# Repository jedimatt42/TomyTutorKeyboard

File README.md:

# TomyTutorKeyboard
A PCBoard design for replacing Tomy Tutor Computer keyboard.

## Status
This is tested. Works great.

## Files

Schematic is here based on KiCAD.

* gerbers - folder with the rendered gerbers
* tomy_tutor_keyboard.scad - OpenSCAD model design file for framing
* tomy_tutor_keyboard.stl - STL file output ready for your favority slicer

# BOM

## 1. Printed Circuit Board

You'll need the bare pcb, see the design files here in this repo.

## 2. 57 MX1A-11NW key switches or equivalent:

The pcboard footprint is specific to these switches. But there are some variety that have the same footprint.

[mouser switches](https://www.mouser.com/ProductDetail/540-MX1A-11NW)

## 3. set of key stabalizers for the wide keys:

[ebay stabalizers](https://www.ebay.com/itm/322528567052?ViewItem=&item=322528567052&ppid=PPX000608&cnac=US&rsta=en_US(en_US)&cust=1SW22173KD939402H&unptid=b421f75c-4e70-11e8-8929-441ea1472df0&t=&cal=b3a4b6dd50c6e&calc=b3a4b6dd50c6e&calf=b3a4b6dd50c6e&unp_tpcid=email-receipt-auction-payment&page=main:email&pgrp=main:email&e=op&mchn=em&s=ci&mail=sys)

## 4. Cable

16 female to female dupont style jumper wires

## 5. 16 pin single inline 2.54mm right angle header

The header on the keyboard pcb is mounted on the underside of the board with the right angle pins facing forward.

## 6. 16 pin single inline 2.54mm straight header

I desoldered and removed the existing film cable connector from the Tomy Tutor motherboard, and replaced it with a row of 16 2.54mm spaced headers.

## 7. Key caps

I used a set of PC keyboard keycaps with a diminutive print. If you can find some with no print, that would be closer to ideal. You'll never find ones that match the Tomy keyboard map.  I found mine on ebay.

## 8. Transparent adhesive printer sheet. 

I printed my key labels on a sheet of adhesive transparency with a laser printer. Then cut out each label and applied it to the keycaps after they were in place. Not the most ideal.

[amazon - Avery self adhesive laminating sheets](https://smile.amazon.com/gp/product/B00006IC7H/ref=ppx_yo_dt_b_search_asin_title?ie=UTF8&psc=1)

NOTE: with regret, I cannot find the document I created with the custom keycap labels...

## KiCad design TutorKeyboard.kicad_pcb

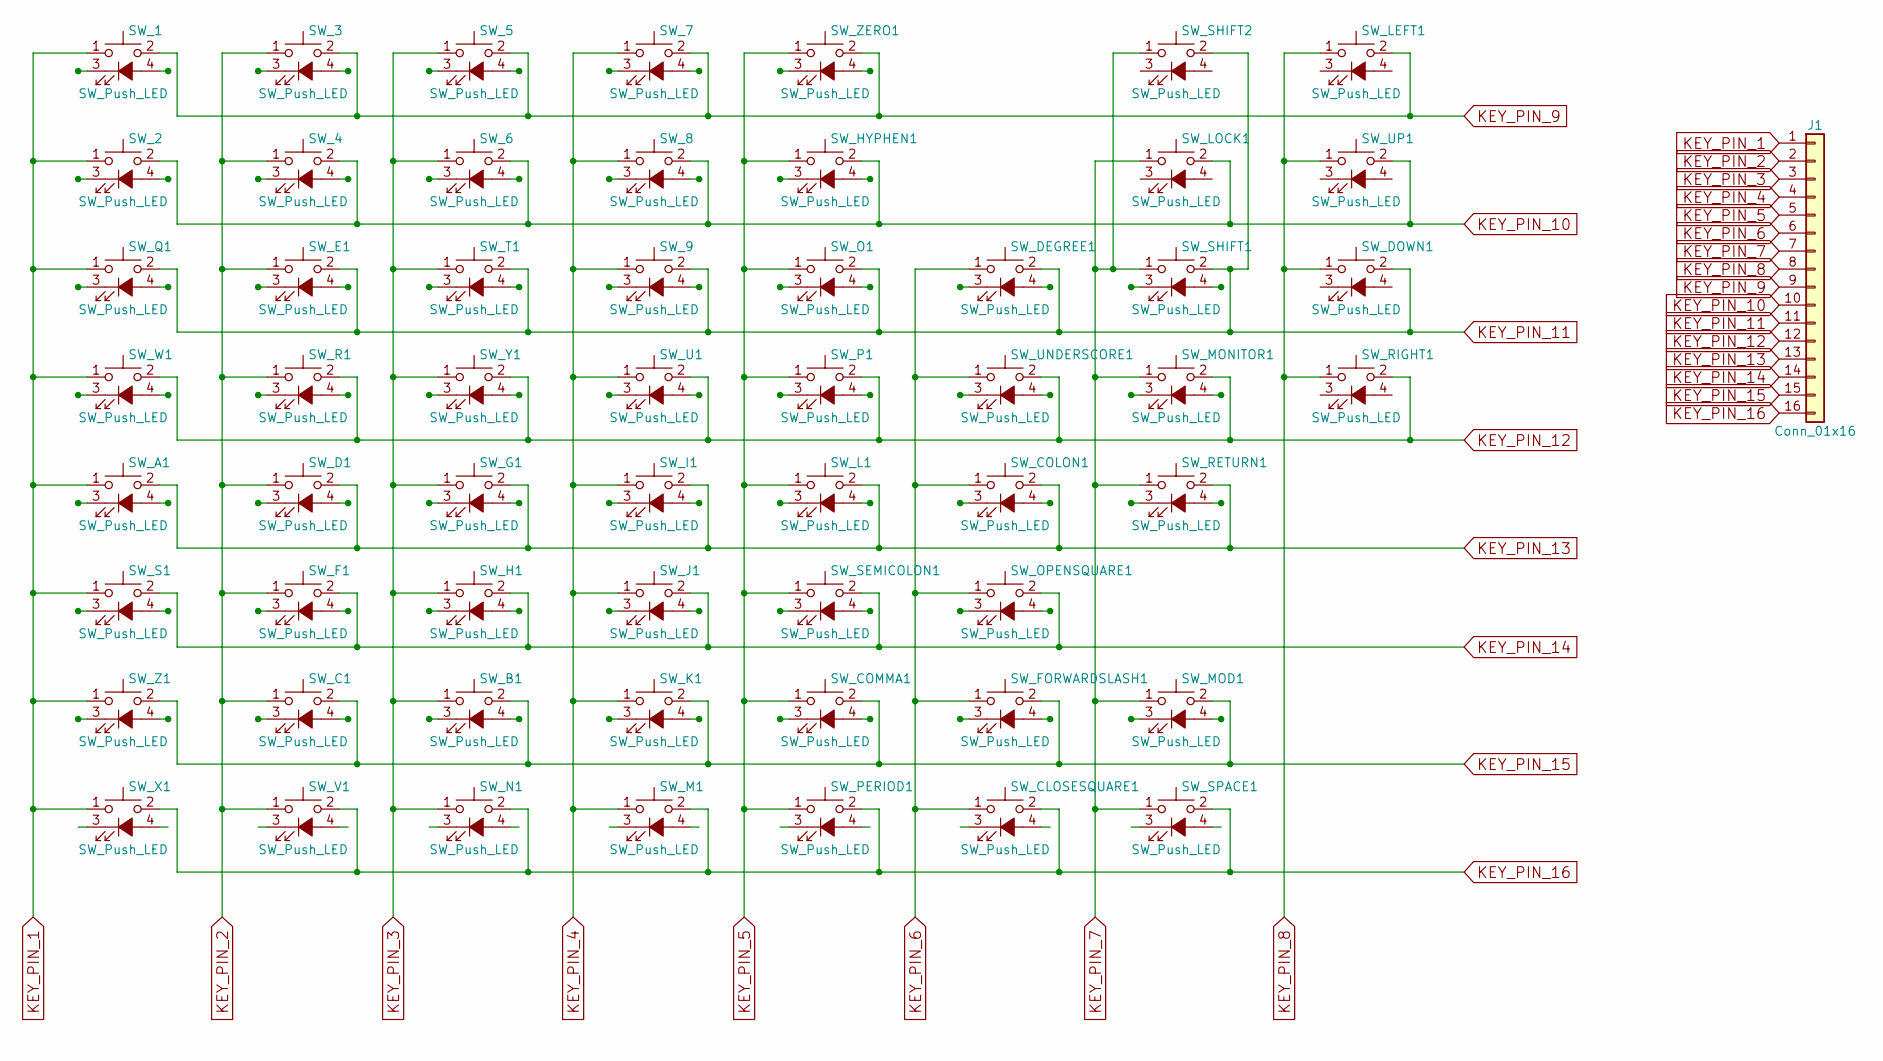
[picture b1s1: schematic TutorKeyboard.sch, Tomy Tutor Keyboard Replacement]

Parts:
J1: Conn_01x16; Pin_Header_Angled_1x16_Pitch2.54mm
SW_1, SW_2, SW_3, SW_4, SW_5, SW_6, SW_7, SW_8, SW_9: SW_Push_LED; SW_Cherry_MX1A_1.00u_PCB
SW_A1: SW_Push_LED; SW_Cherry_MX1A_1.00u_PCB
SW_B1: SW_Push_LED; SW_Cherry_MX1A_1.00u_PCB
SW_C1: SW_Push_LED; SW_Cherry_MX1A_1.00u_PCB
SW_CLOSESQUARE1: SW_Push_LED; SW_Cherry_MX1A_1.00u_PCB
SW_COLON1: SW_Push_LED; SW_Cherry_MX1A_1.00u_PCB
SW_COMMA1: SW_Push_LED; SW_Cherry_MX1A_1.00u_PCB
SW_D1: SW_Push_LED; SW_Cherry_MX1A_1.00u_PCB
SW_DEGREE1: SW_Push_LED; SW_Cherry_MX1A_1.00u_PCB
SW_DOWN1: SW_Push_LED; SW_Cherry_MX1A_1.00u_PCB
SW_E1: SW_Push_LED; SW_Cherry_MX1A_1.00u_PCB
SW_F1: SW_Push_LED; SW_Cherry_MX1A_1.00u_PCB
SW_FORWARDSLASH1: SW_Push_LED; SW_Cherry_MX1A_1.00u_PCB
SW_G1: SW_Push_LED; SW_Cherry_MX1A_1.00u_PCB
SW_H1: SW_Push_LED; SW_Cherry_MX1A_1.00u_PCB
SW_HYPHEN1: SW_Push_LED; SW_Cherry_MX1A_1.00u_PCB
SW_I1: SW_Push_LED; SW_Cherry_MX1A_1.00u_PCB
SW_J1: SW_Push_LED; SW_Cherry_MX1A_1.00u_PCB
SW_K1: SW_Push_LED; SW_Cherry_MX1A_1.00u_PCB
SW_L1: SW_Push_LED; SW_Cherry_MX1A_1.00u_PCB
SW_LEFT1: SW_Push_LED; SW_Cherry_MX1A_1.00u_PCB
SW_LOCK1: SW_Push_LED; SW_Cherry_MX1A_1.75u_PCB
SW_M1: SW_Push_LED; SW_Cherry_MX1A_1.00u_PCB
SW_MOD1: SW_Push_LED; SW_Cherry_MX1A_1.00u_PCB
SW_MONITOR1: SW_Push_LED; SW_Cherry_MX1A_1.00u_PCB
SW_N1: SW_Push_LED; SW_Cherry_MX1A_1.00u_PCB
SW_O1: SW_Push_LED; SW_Cherry_MX1A_1.00u_PCB
SW_OPENSQUARE1: SW_Push_LED; SW_Cherry_MX1A_1.00u_PCB
SW_P1: SW_Push_LED; SW_Cherry_MX1A_1.00u_PCB
SW_PERIOD1: SW_Push_LED; SW_Cherry_MX1A_1.00u_PCB
SW_Q1: SW_Push_LED; SW_Cherry_MX1A_1.00u_PCB
SW_R1: SW_Push_LED; SW_Cherry_MX1A_1.00u_PCB
SW_RETURN1: SW_Push_LED; SW_Cherry_MX1A_2.25u_PCB
SW_RIGHT1: SW_Push_LED; SW_Cherry_MX1A_1.00u_PCB
SW_S1: SW_Push_LED; SW_Cherry_MX1A_1.00u_PCB
SW_SEMICOLON1: SW_Push_LED; SW_Cherry_MX1A_1.00u_PCB
SW_SHIFT1: SW_Push_LED; SW_Cherry_MX1A_2.25u_PCB
SW_SHIFT2: SW_Push_LED; SW_Cherry_MX1A_2.75u_PCB
SW_SPACE1: SW_Push_LED; SW_Cherry_MX1A_6.25u_PCB
SW_T1: SW_Push_LED; SW_Cherry_MX1A_1.00u_PCB
SW_U1: SW_Push_LED; SW_Cherry_MX1A_1.00u_PCB
SW_UNDERSCORE1: SW_Push_LED; SW_Cherry_MX1A_1.00u_PCB
SW_UP1: SW_Push_LED; SW_Cherry_MX1A_1.00u_PCB
SW_V1: SW_Push_LED; SW_Cherry_MX1A_1.00u_PCB
SW_W1: SW_Push_LED; SW_Cherry_MX1A_1.00u_PCB
SW_X1: SW_Push_LED; SW_Cherry_MX1A_1.00u_PCB
SW_Y1: SW_Push_LED; SW_Cherry_MX1A_1.00u_PCB
SW_Z1: SW_Push_LED; SW_Cherry_MX1A_1.00u_PCB
SW_ZERO1: SW_Push_LED; SW_Cherry_MX1A_1.00u_PCB

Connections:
KEY_PIN_1: J1.1, SW_1.1, SW_2.1, SW_A1.1, SW_Q1.1, SW_S1.1, SW_W1.1, SW_X1.1, SW_Z1.1
KEY_PIN_2: J1.2, SW_3.1, SW_4.1, SW_C1.1, SW_D1.1, SW_E1.1, SW_F1.1, SW_R1.1, SW_V1.1
KEY_PIN_3: J1.3, SW_5.1, SW_6.1, SW_B1.1, SW_G1.1, SW_H1.1, SW_N1.1, SW_T1.1, SW_Y1.1
KEY_PIN_4: J1.4, SW_7.1, SW_8.1, SW_9.1, SW_I1.1, SW_J1.1, SW_K1.1, SW_M1.1, SW_U1.1
KEY_PIN_5: J1.5, SW_COMMA1.1, SW_HYPHEN1.1, SW_L1.1, SW_O1.1, SW_P1.1, SW_PERIOD1.1, SW_SEMICOLON1.1, SW_ZERO1.1
KEY_PIN_6: J1.6, SW_CLOSESQUARE1.1, SW_COLON1.1, SW_DEGREE1.1, SW_FORWARDSLASH1.1, SW_OPENSQUARE1.1, SW_UNDERSCORE1.1
KEY_PIN_7: J1.7, SW_LOCK1.1, SW_MOD1.1, SW_MONITOR1.1, SW_RETURN1.1, SW_SHIFT1.1, SW_SHIFT2.1, SW_SPACE1.1
KEY_PIN_8: J1.8, SW_DOWN1.1, SW_LEFT1.1, SW_RIGHT1.1, SW_UP1.1
KEY_PIN_9: J1.9, SW_1.2, SW_3.2, SW_5.2, SW_7.2, SW_LEFT1.2, SW_ZERO1.2
KEY_PIN_10: J1.10, SW_2.2, SW_4.2, SW_6.2, SW_8.2, SW_HYPHEN1.2, SW_LOCK1.2, SW_UP1.2
KEY_PIN_11: J1.11, SW_9.2, SW_DEGREE1.2, SW_DOWN1.2, SW_E1.2, SW_O1.2, SW_Q1.2, SW_SHIFT1.2, SW_SHIFT2.2, SW_T1.2
KEY_PIN_12: J1.12, SW_MONITOR1.2, SW_P1.2, SW_R1.2, SW_RIGHT1.2, SW_U1.2, SW_UNDERSCORE1.2, SW_W1.2, SW_Y1.2
KEY_PIN_13: J1.13, SW_A1.2, SW_COLON1.2, SW_D1.2, SW_G1.2, SW_I1.2, SW_L1.2, SW_RETURN1.2
KEY_PIN_14: J1.14, SW_F1.2, SW_H1.2, SW_J1.2, SW_OPENSQUARE1.2, SW_S1.2, SW_SEMICOLON1.2
KEY_PIN_15: J1.15, SW_B1.2, SW_C1.2, SW_COMMA1.2, SW_FORWARDSLASH1.2, SW_K1.2, SW_MOD1.2, SW_Z1.2
KEY_PIN_16: J1.16, SW_CLOSESQUARE1.2, SW_M1.2, SW_N1.2, SW_PERIOD1.2, SW_SPACE1.2, SW_V1.2, SW_X1.2

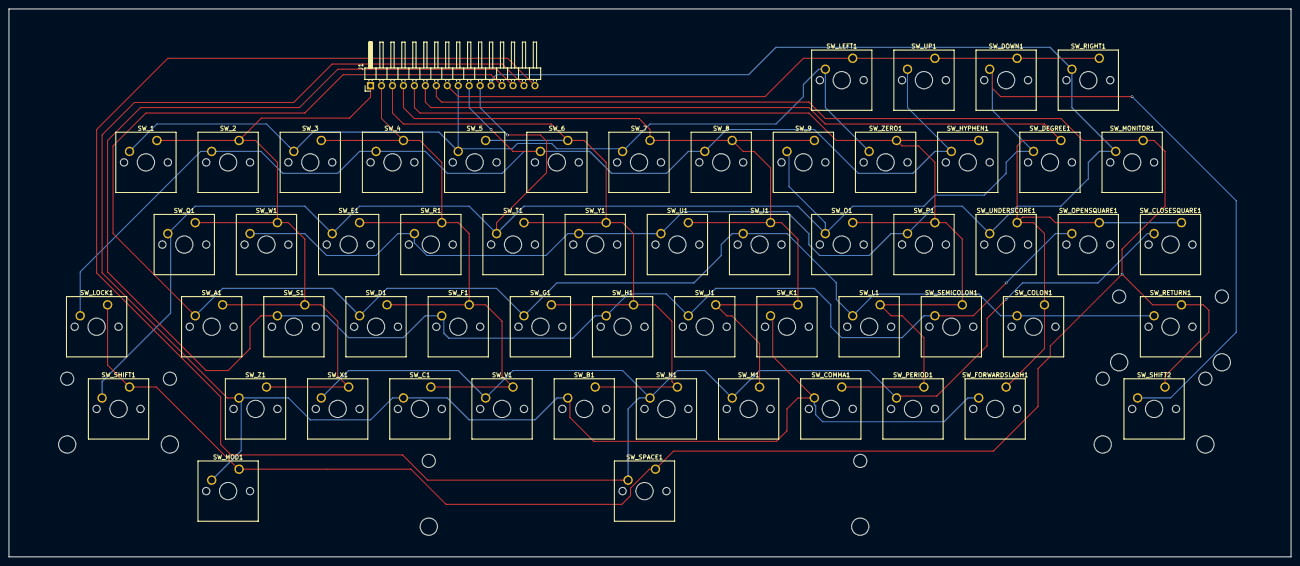
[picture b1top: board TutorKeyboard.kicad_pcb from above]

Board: 2 copper layers, 297.2 x 127.0 mm, 58 parts (0 on the bottom side), 16 nets.

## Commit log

2018-01-19 slightly modernized.
2018-01-19 Everything needs a license to be open.
2019-02-07 final bits and artifacts if others want to print boards
2019-02-07 add openscad model source, and stl file - probably needs to be cut up for printing
2019-02-07 update status.
